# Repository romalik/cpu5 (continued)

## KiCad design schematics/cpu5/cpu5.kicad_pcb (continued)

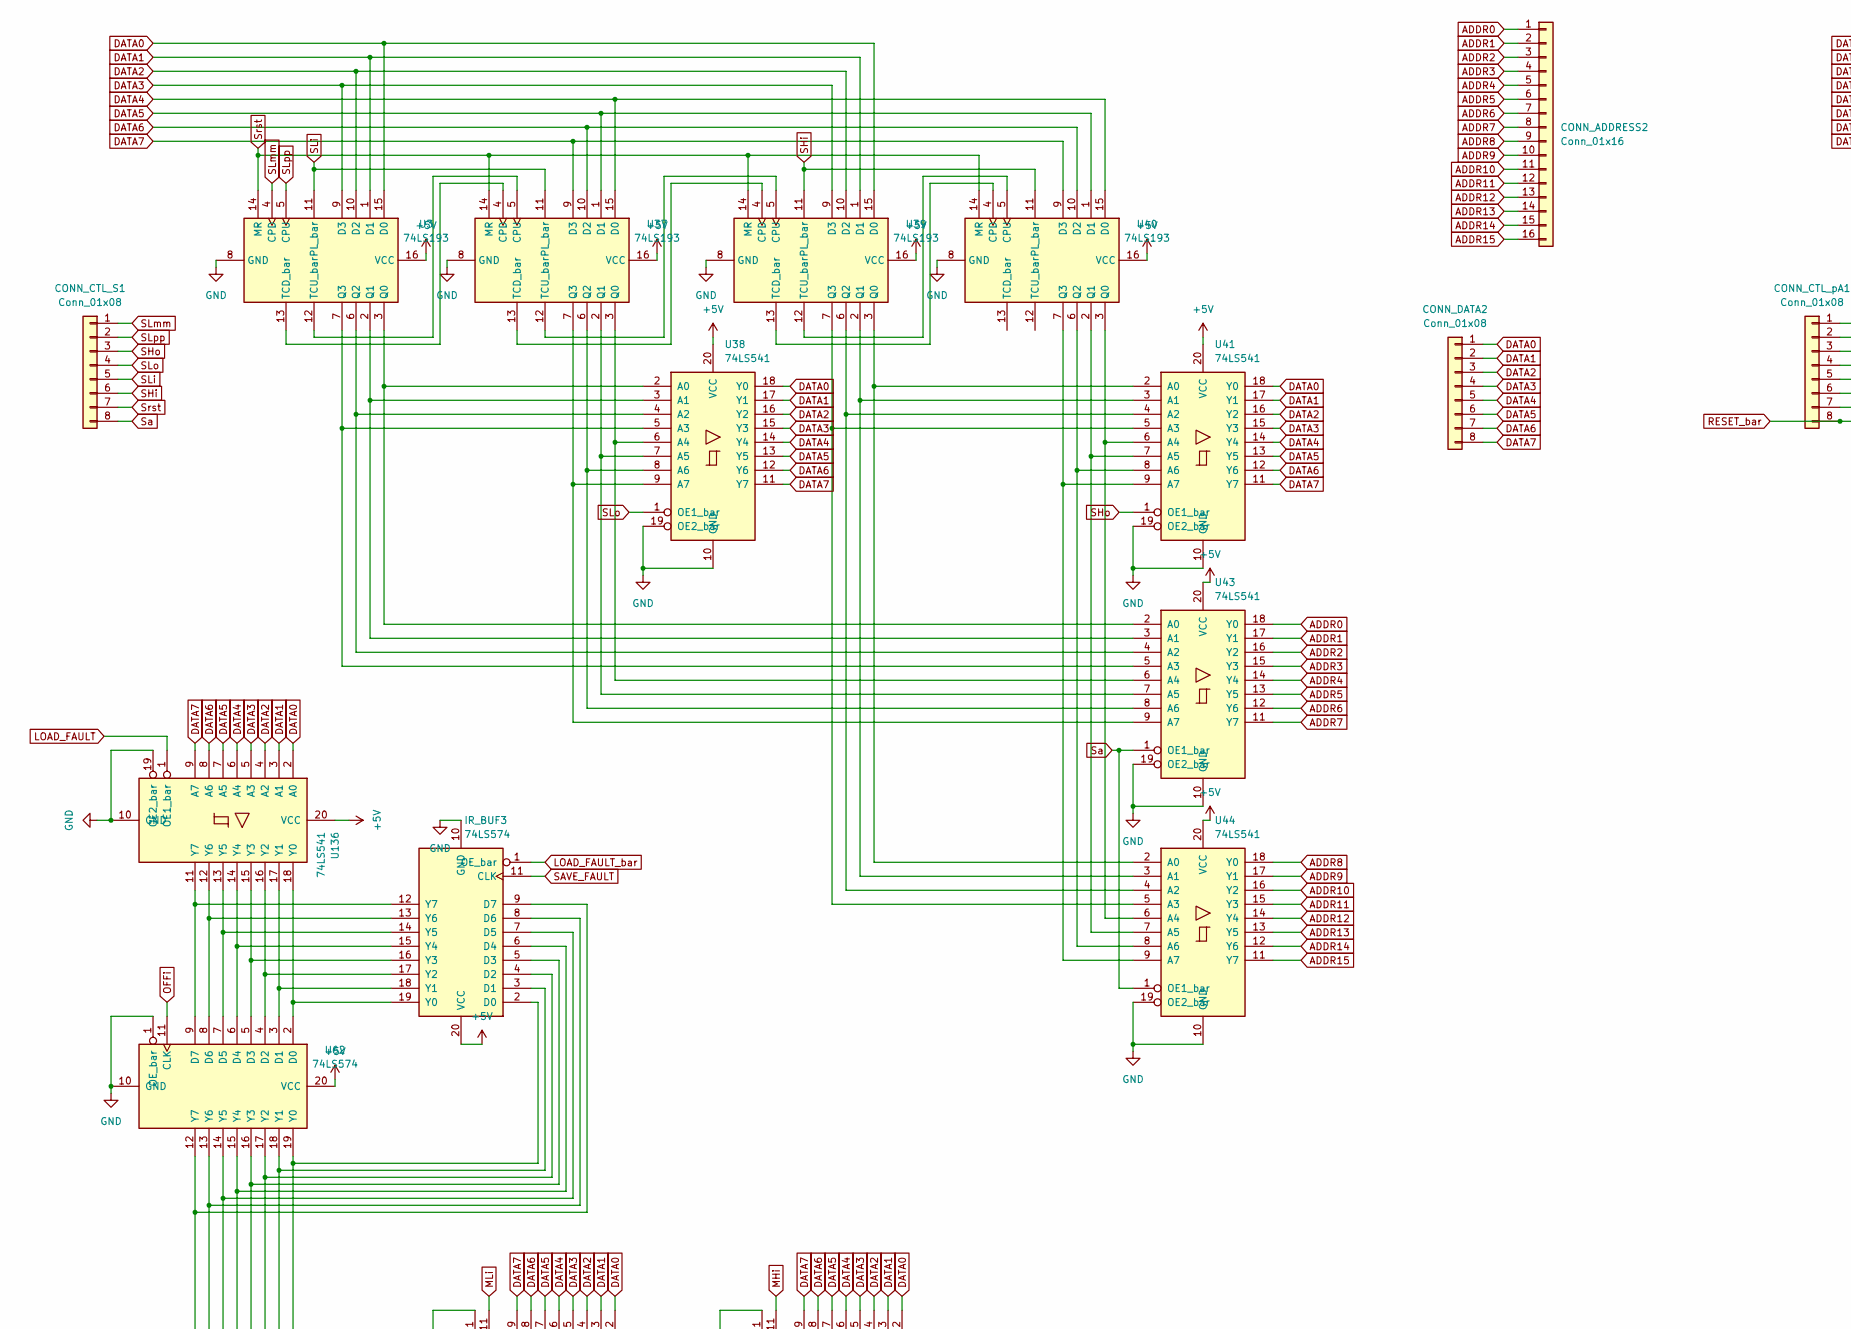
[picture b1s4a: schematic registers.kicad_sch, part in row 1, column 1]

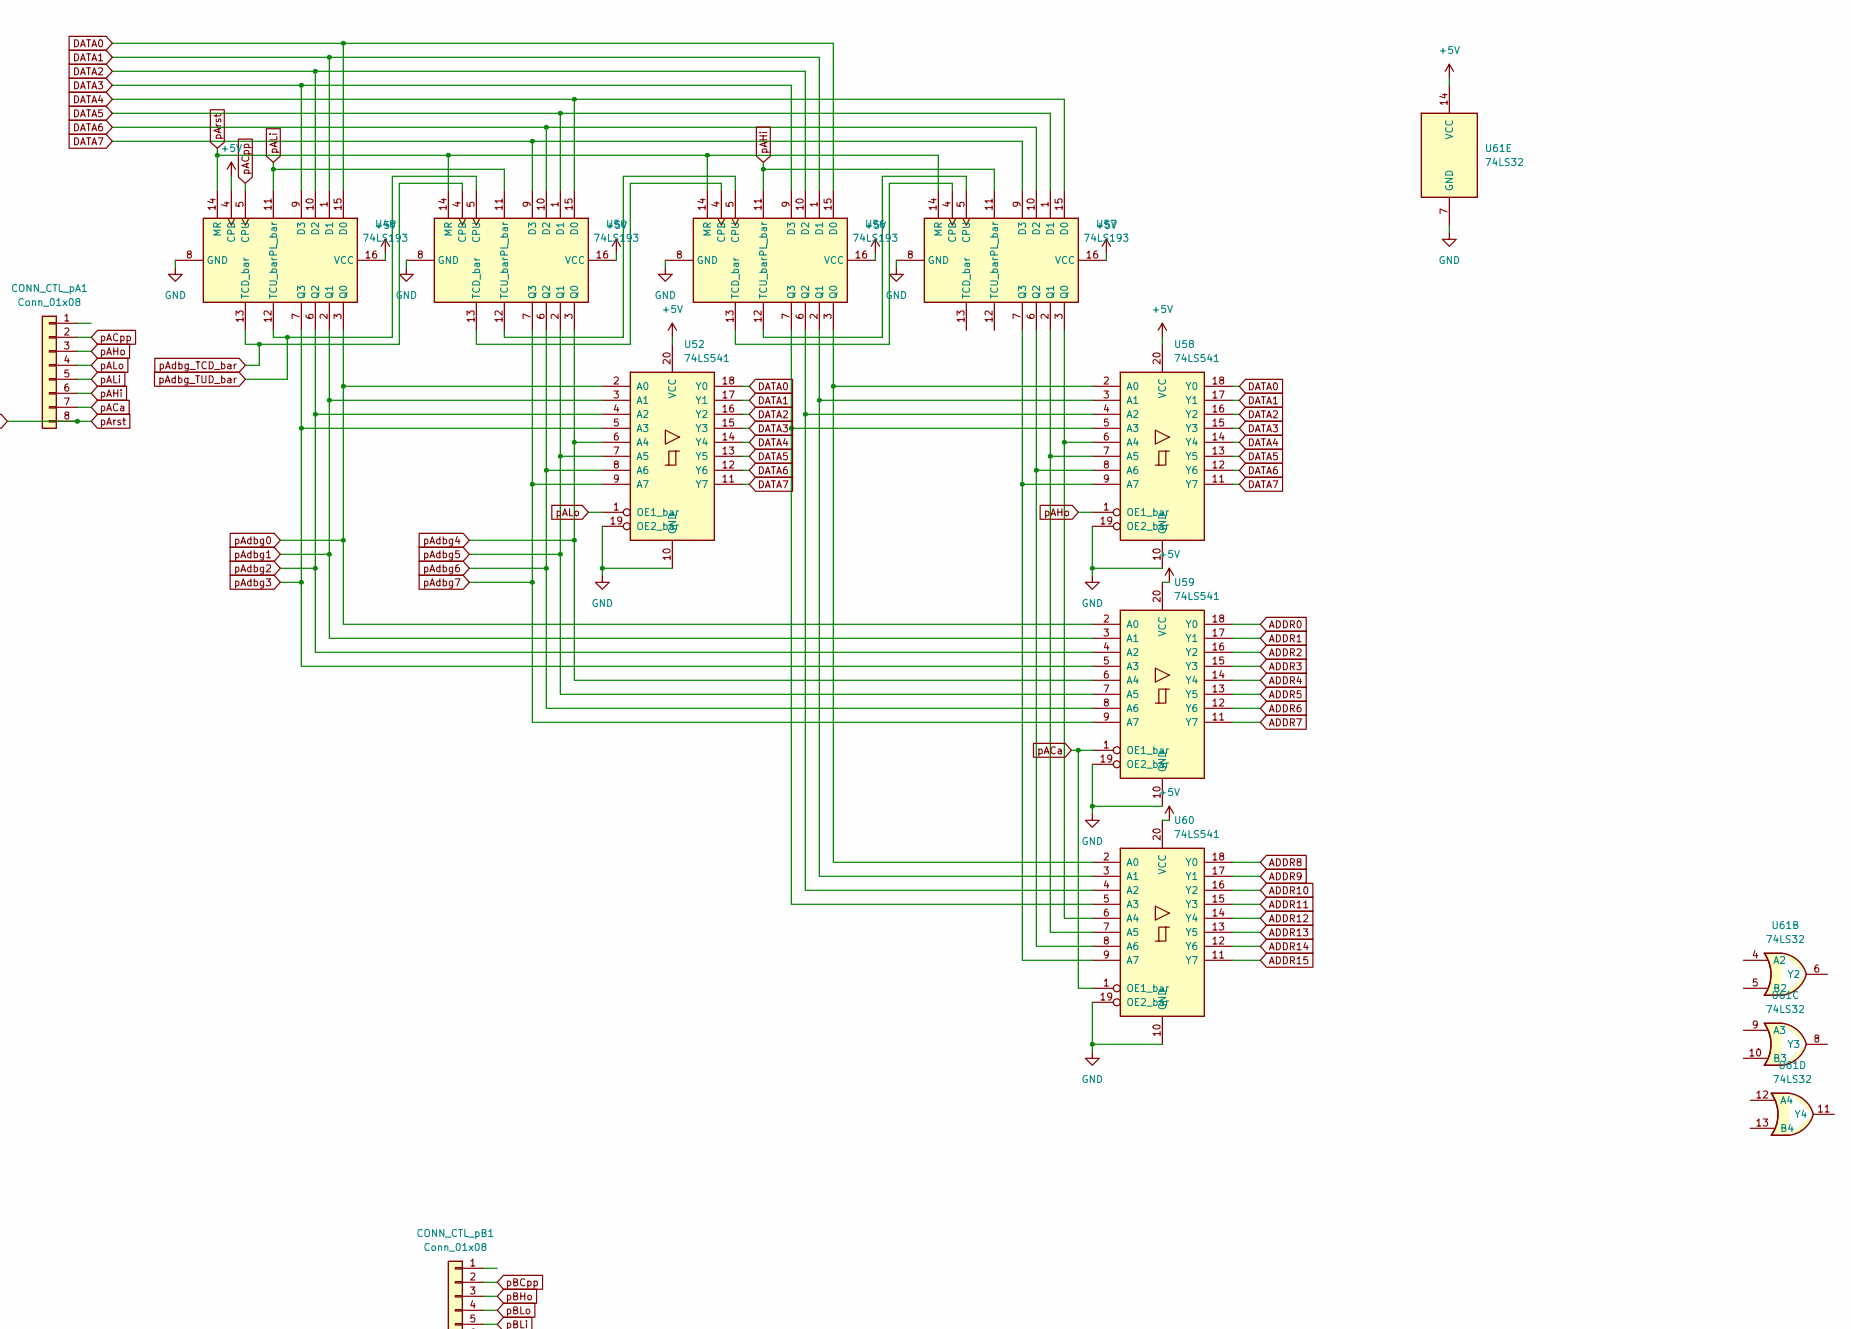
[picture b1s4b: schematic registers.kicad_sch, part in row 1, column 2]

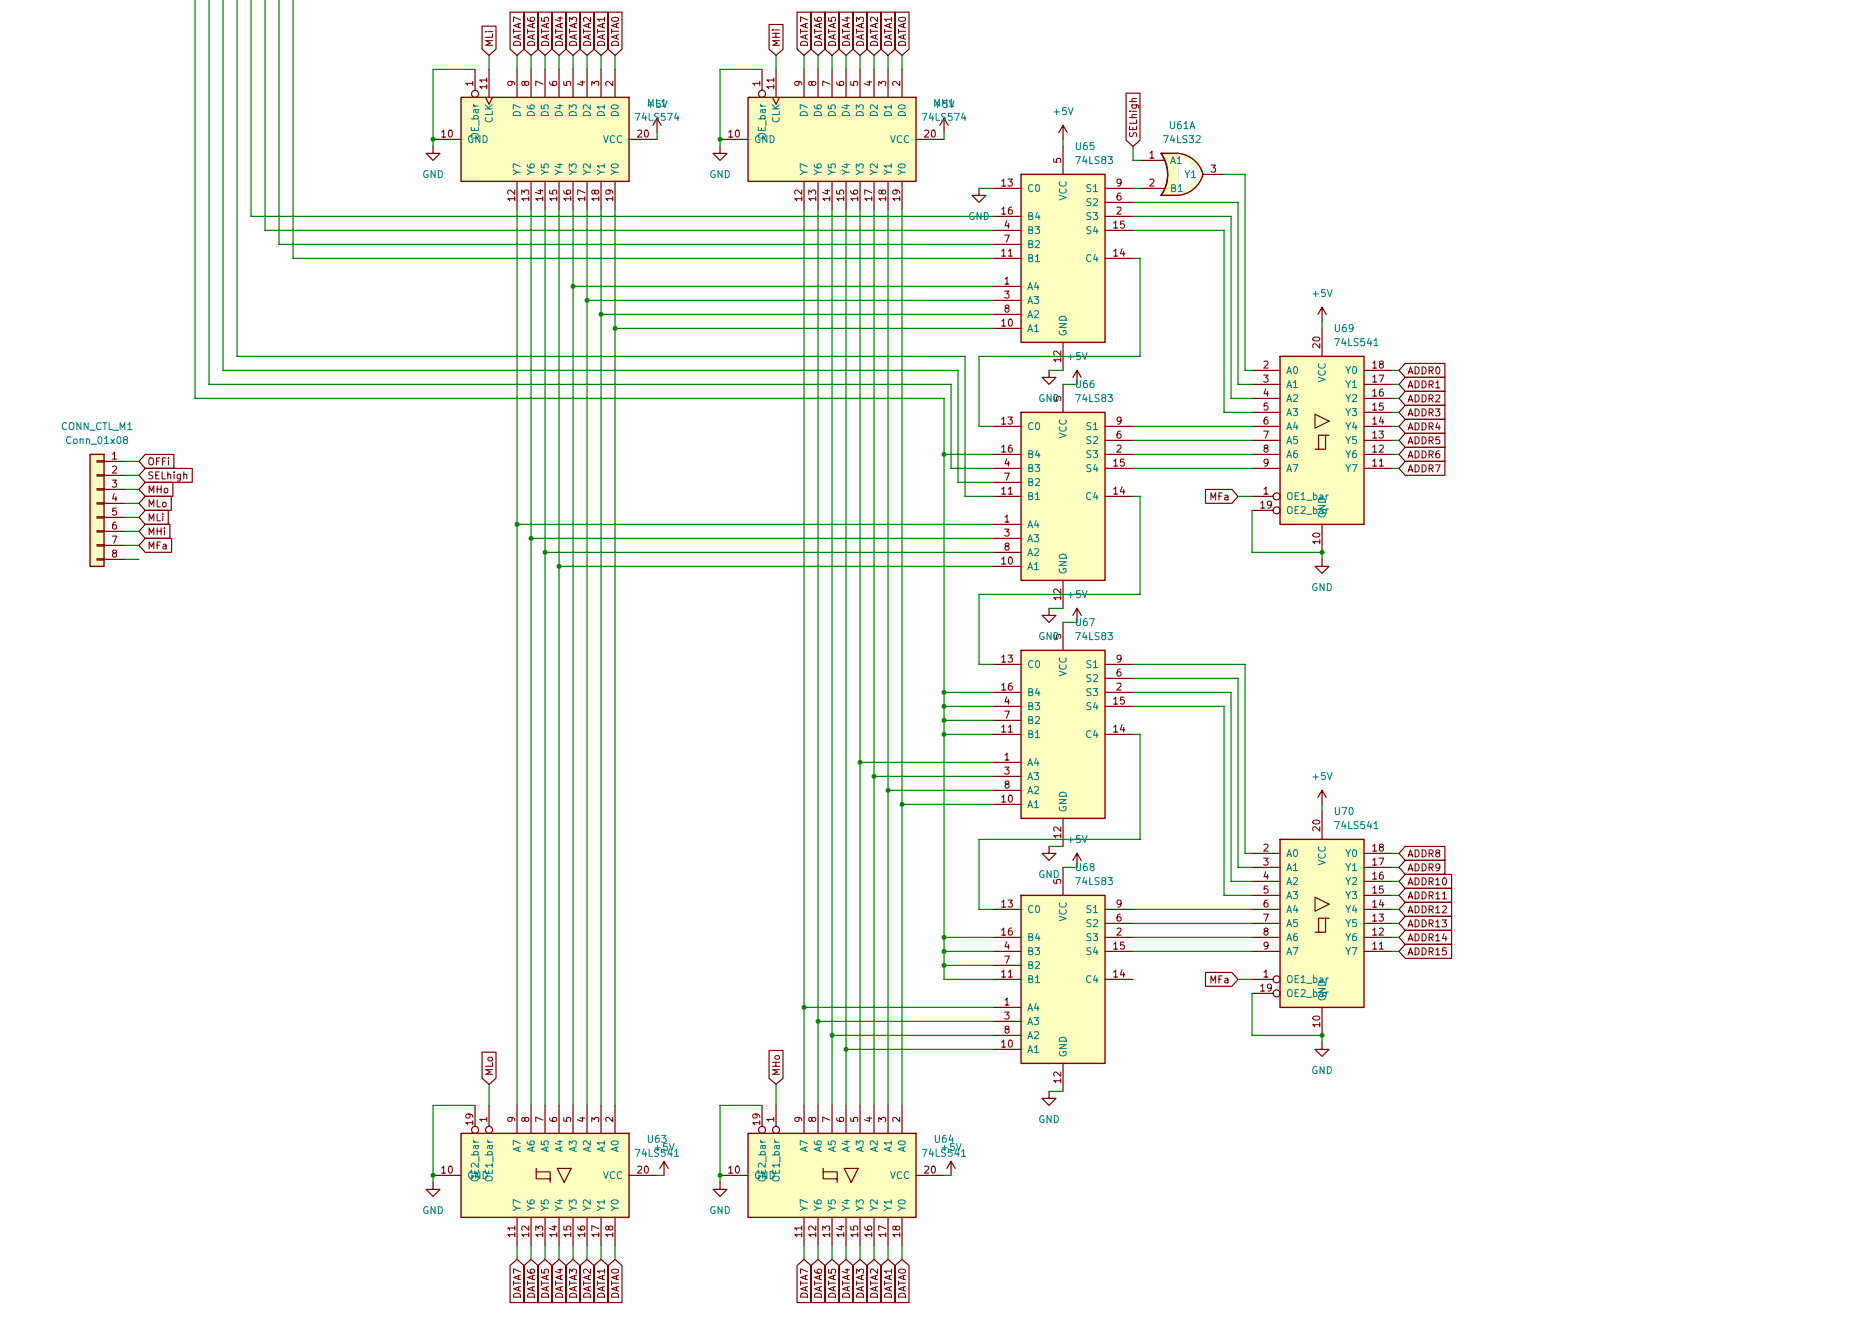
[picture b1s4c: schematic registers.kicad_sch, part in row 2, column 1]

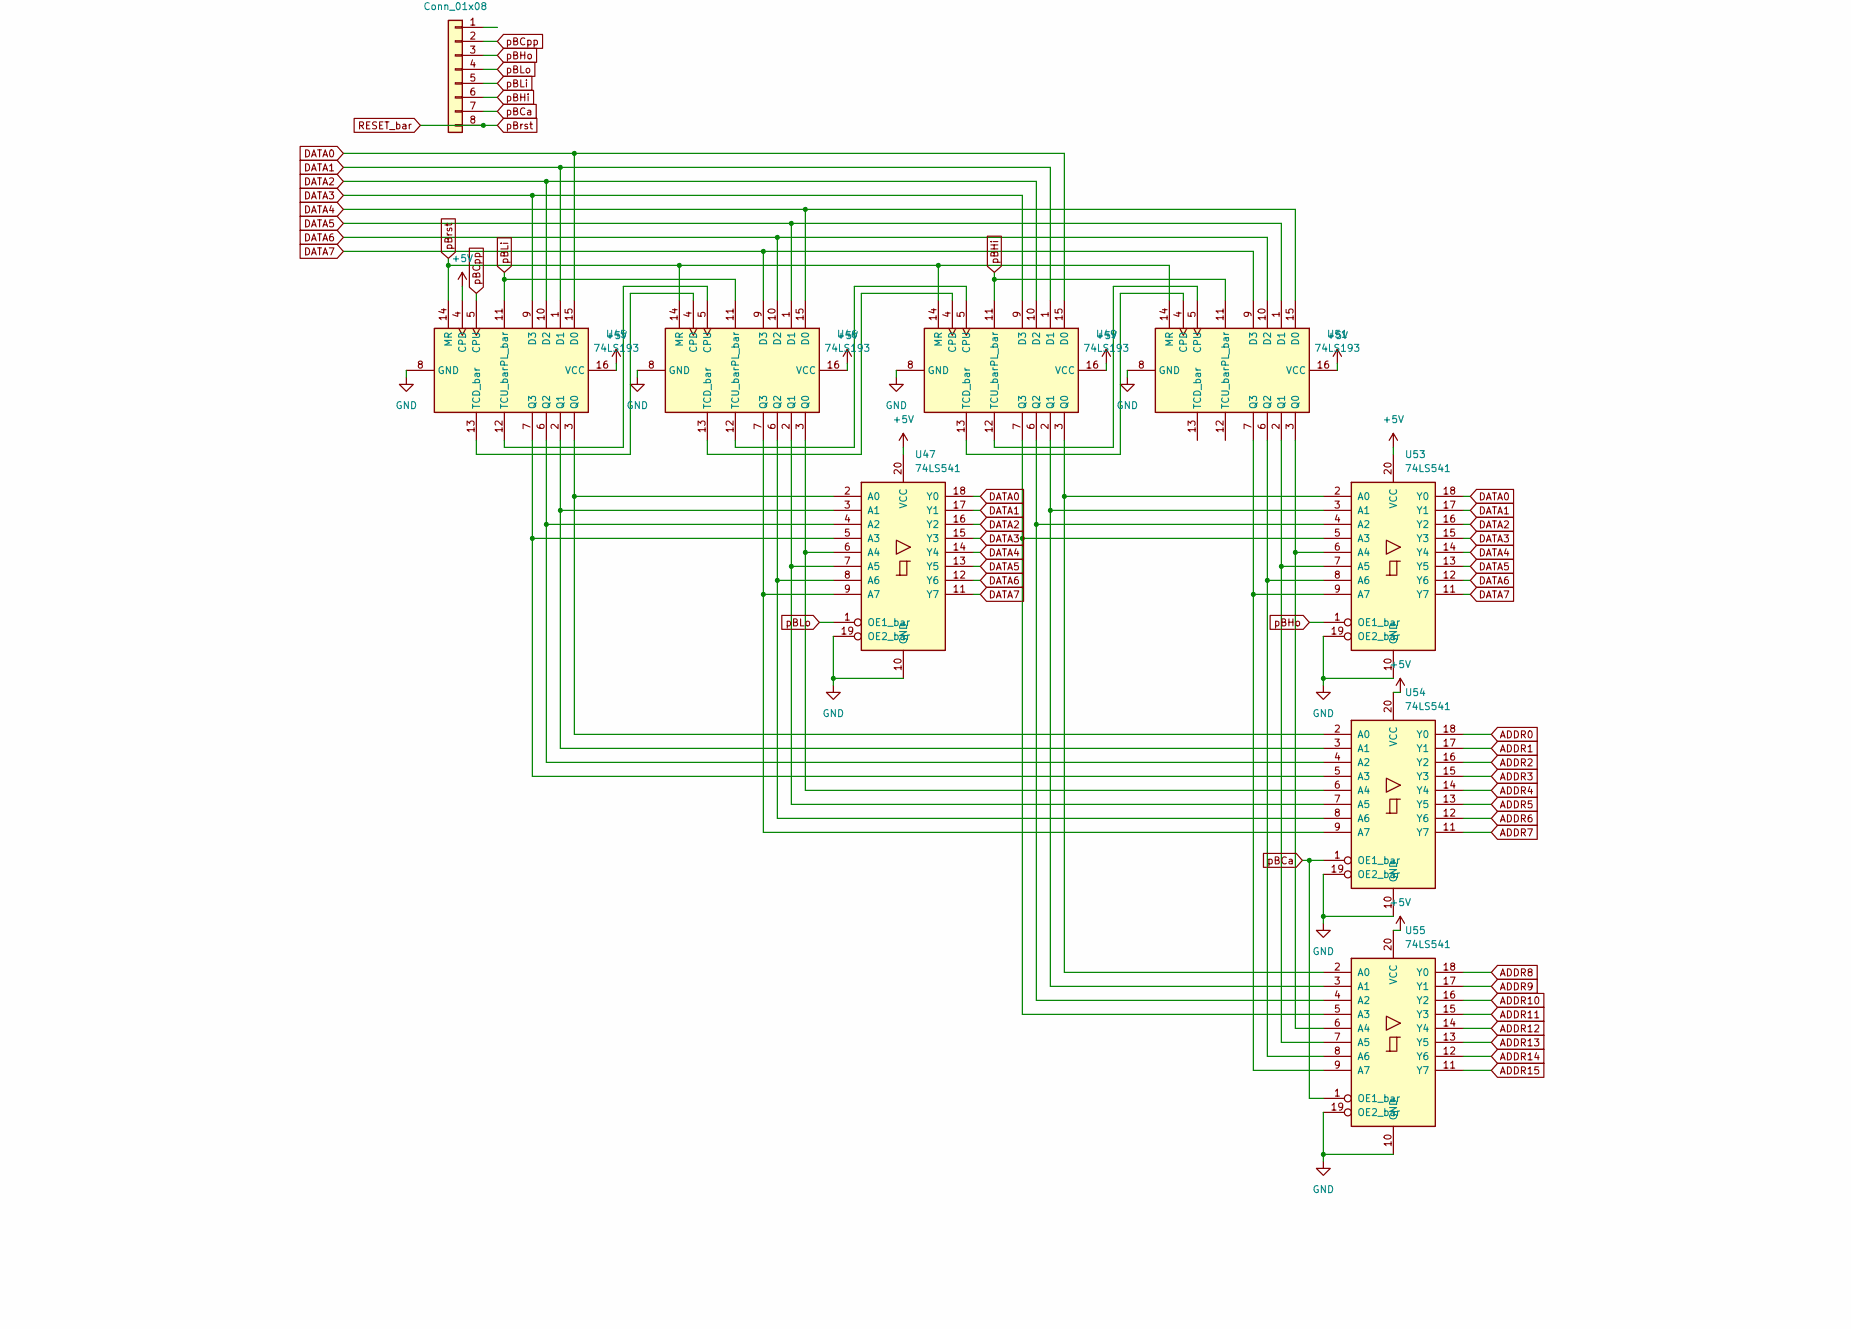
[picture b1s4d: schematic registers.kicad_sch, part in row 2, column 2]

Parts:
CONN_ADDRESS2: Conn_01x16; PinHeader_1x16_P2.54mm_Vertical
CONN_CTL_M1: Conn_01x08; PinHeader_1x08_P2.54mm_Vertical
CONN_CTL_S1: Conn_01x08; PinHeader_1x08_P2.54mm_Vertical
CONN_CTL_pA1: Conn_01x08; PinHeader_1x08_P2.54mm_Vertical
CONN_CTL_pB1: Conn_01x08; PinHeader_1x08_P2.54mm_Vertical
CONN_DATA2: Conn_01x08; PinHeader_1x08_P2.54mm_Vertical
IR_BUF3: 74LS574; DIP-20_W7.62mm
MH1: 74LS574; DIP-20_W7.62mm
ML1: 74LS574; DIP-20_W7.62mm
U3, U37, U39, U40, U45, U46, U48, U49, U50, U51, U56, U57: 74LS193; DIP-16_W7.62mm
U38, U41, U43, U44, U47, U52, U53, U54, U55, U58, U59, U60, U63, U64, U69, U70, U136: 74LS541; DIP-20_W7.62mm
U61: 74LS32; DIP-14_W7.62mm
U62: 74LS574; DIP-20_W7.62mm
U65, U66, U67, U68: 74LS83; DIP-16_W7.62mm

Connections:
+5V: IR_BUF3.20 (VCC), MH1.20 (VCC), ML1.20 (VCC), U3.16 (VCC), U37.16 (VCC), U38.20 (VCC), U39.16 (VCC), U40.16 (VCC), U41.20 (VCC), U43.20 (VCC), U44.20 (VCC), U45.4 (CPD), U45.16 (VCC), U46.16 (VCC), U47.20 (VCC), U48.4 (CPD), U48.16 (VCC), U49.16 (VCC), U50.16 (VCC), U51.16 (VCC), U52.20 (VCC), U53.20 (VCC), U54.20 (VCC), U55.20 (VCC), U56.16 (VCC), U57.16 (VCC), U58.20 (VCC), U59.20 (VCC), U60.20 (VCC), U61.14 (VCC), U62.20 (VCC), U63.20 (VCC), U64.20 (VCC), U65.5 (VCC), U66.5 (VCC), U67.5 (VCC), U68.5 (VCC), U69.20 (VCC), U70.20 (VCC), U136.20 (VCC); also elsewhere on the board
ADDR0: CONN_ADDRESS2.1, U43.18 (Y0), U54.18 (Y0), U59.18 (Y0), U69.18 (Y0); also elsewhere on the board
ADDR1: CONN_ADDRESS2.2, U43.17 (Y1), U54.17 (Y1), U59.17 (Y1), U69.17 (Y1); also elsewhere on the board
ADDR2: CONN_ADDRESS2.3, U43.16 (Y2), U54.16 (Y2), U59.16 (Y2), U69.16 (Y2); also elsewhere on the board
ADDR3: CONN_ADDRESS2.4, U43.15 (Y3), U54.15 (Y3), U59.15 (Y3), U69.15 (Y3); also elsewhere on the board
ADDR4: CONN_ADDRESS2.5, U43.14 (Y4), U54.14 (Y4), U59.14 (Y4), U69.14 (Y4); also elsewhere on the board
ADDR5: CONN_ADDRESS2.6, U43.13 (Y5), U54.13 (Y5), U59.13 (Y5), U69.13 (Y5); also elsewhere on the board
ADDR6: CONN_ADDRESS2.7, U43.12 (Y6), U54.12 (Y6), U59.12 (Y6), U69.12 (Y6); also elsewhere on the board
ADDR7: CONN_ADDRESS2.8, U43.11 (Y7), U54.11 (Y7), U59.11 (Y7), U69.11 (Y7); also elsewhere on the board
ADDR8: CONN_ADDRESS2.9, U44.18 (Y0), U55.18 (Y0), U60.18 (Y0), U70.18 (Y0); also elsewhere on the board
ADDR9: CONN_ADDRESS2.10, U44.17 (Y1), U55.17 (Y1), U60.17 (Y1), U70.17 (Y1); also elsewhere on the board
ADDR10: CONN_ADDRESS2.11, U44.16 (Y2), U55.16 (Y2), U60.16 (Y2), U70.16 (Y2); also elsewhere on the board
ADDR11: CONN_ADDRESS2.12, U44.15 (Y3), U55.15 (Y3), U60.15 (Y3), U70.15 (Y3); also elsewhere on the board
ADDR12: CONN_ADDRESS2.13, U44.14 (Y4), U55.14 (Y4), U60.14 (Y4), U70.14 (Y4); also elsewhere on the board
ADDR13: CONN_ADDRESS2.14, U44.13 (Y5), U55.13 (Y5), U60.13 (Y5), U70.13 (Y5); also elsewhere on the board
ADDR14: CONN_ADDRESS2.15, U44.12 (Y6), U55.12 (Y6), U60.12 (Y6), U70.12 (Y6); also elsewhere on the board
ADDR15: CONN_ADDRESS2.16, U44.11 (Y7), U55.11 (Y7), U60.11 (Y7), U70.11 (Y7); also elsewhere on the board
DATA0: CONN_DATA2.1, MH1.2 (D0), ML1.2 (D0), U3.15 (D0), U38.18 (Y0), U39.15 (D0), U41.18 (Y0), U45.15 (D0), U47.18 (Y0), U48.15 (D0), U49.15 (D0), U52.18 (Y0), U53.18 (Y0), U56.15 (D0), U58.18 (Y0), U63.18 (Y0), U64.18 (Y0), U136.2 (A0); also elsewhere on the board
DATA1: CONN_DATA2.2, MH1.3 (D1), ML1.3 (D1), U3.1 (D1), U38.17 (Y1), U39.1 (D1), U41.17 (Y1), U45.1 (D1), U47.17 (Y1), U48.1 (D1), U49.1 (D1), U52.17 (Y1), U53.17 (Y1), U56.1 (D1), U58.17 (Y1), U63.17 (Y1), U64.17 (Y1), U136.3 (A1); also elsewhere on the board
DATA2: CONN_DATA2.3, MH1.4 (D2), ML1.4 (D2), U3.10 (D2), U38.16 (Y2), U39.10 (D2), U41.16 (Y2), U45.10 (D2), U47.16 (Y2), U48.10 (D2), U49.10 (D2), U52.16 (Y2), U53.16 (Y2), U56.10 (D2), U58.16 (Y2), U63.16 (Y2), U64.16 (Y2), U136.4 (A2); also elsewhere on the board
DATA3: CONN_DATA2.4, MH1.5 (D3), ML1.5 (D3), U3.9 (D3), U38.15 (Y3), U39.9 (D3), U41.15 (Y3), U45.9 (D3), U47.15 (Y3), U48.9 (D3), U49.9 (D3), U52.15 (Y3), U53.15 (Y3), U56.9 (D3), U58.15 (Y3), U63.15 (Y3), U64.15 (Y3), U136.5 (A3); also elsewhere on the board
DATA4: CONN_DATA2.5, MH1.6 (D4), ML1.6 (D4), U37.15 (D0), U38.14 (Y4), U40.15 (D0), U41.14 (Y4), U46.15 (D0), U47.14 (Y4), U50.15 (D0), U51.15 (D0), U52.14 (Y4), U53.14 (Y4), U57.15 (D0), U58.14 (Y4), U63.14 (Y4), U64.14 (Y4), U136.6 (A4); also elsewhere on the board
DATA5: CONN_DATA2.6, MH1.7 (D5), ML1.7 (D5), U37.1 (D1), U38.13 (Y5), U40.1 (D1), U41.13 (Y5), U46.1 (D1), U47.13 (Y5), U50.1 (D1), U51.1 (D1), U52.13 (Y5), U53.13 (Y5), U57.1 (D1), U58.13 (Y5), U63.13 (Y5), U64.13 (Y5), U136.7 (A5); also elsewhere on the board
DATA6: CONN_DATA2.7, MH1.8 (D6), ML1.8 (D6), U37.10 (D2), U38.12 (Y6), U40.10 (D2), U41.12 (Y6), U46.10 (D2), U47.12 (Y6), U50.10 (D2), U51.10 (D2), U52.12 (Y6), U53.12 (Y6), U57.10 (D2), U58.12 (Y6), U63.12 (Y6), U64.12 (Y6), U136.8 (A6); also elsewhere on the board
DATA7: CONN_DATA2.8, MH1.9 (D7), ML1.9 (D7), U37.9 (D3), U38.11 (Y7), U40.9 (D3), U41.11 (Y7), U46.9 (D3), U47.11 (Y7), U50.9 (D3), U51.9 (D3), U52.11 (Y7), U53.11 (Y7), U57.9 (D3), U58.11 (Y7), U63.11 (Y7), U64.11 (Y7), U136.9 (A7); also elsewhere on the board
GND: IR_BUF3.10 (GND), MH1.1 (OE_bar), MH1.10 (GND), ML1.1 (OE_bar), ML1.10 (GND), U3.8 (GND), U37.8 (GND), U38.10 (GND), U38.19 (OE2_bar), U39.8 (GND), U40.8 (GND), U41.10 (GND), U41.19 (OE2_bar), U43.10 (GND), U43.19 (OE2_bar), U44.10 (GND), U44.19 (OE2_bar), U45.8 (GND), U46.8 (GND), U47.10 (GND), U47.19 (OE2_bar), U48.8 (GND), U49.8 (GND), U50.8 (GND), U51.8 (GND), U52.10 (GND), U52.19 (OE2_bar), U53.10 (GND), U53.19 (OE2_bar), U54.10 (GND), U54.19 (OE2_bar), U55.10 (GND), U55.19 (OE2_bar), U56.8 (GND), U57.8 (GND), U58.10 (GND), U58.19 (OE2_bar), U59.10 (GND), U59.19 (OE2_bar), U60.10 (GND), U60.19 (OE2_bar), U61.7 (GND), U62.1 (OE_bar), U62.10 (GND), U63.10 (GND), U63.19 (OE2_bar), U64.10 (GND), U64.19 (OE2_bar), U65.12 (GND), U65.13 (C0), U66.12 (GND), U67.12 (GND), U68.12 (GND), U69.10 (GND), U69.19 (OE2_bar), U70.10 (GND), U70.19 (OE2_bar), U136.10 (GND), U136.19 (OE2_bar); also elsewhere on the board
LOAD_FAULT: U136.1 (OE1_bar); also elsewhere on the board
LOAD_FAULT_bar: IR_BUF3.1 (OE_bar); also elsewhere on the board
MFa: CONN_CTL_M1.7, U69.1 (OE1_bar), U70.1 (OE1_bar); also elsewhere on the board
MHi: CONN_CTL_M1.6, MH1.11 (CLK); also elsewhere on the board
MHo: CONN_CTL_M1.3, U64.1 (OE1_bar); also elsewhere on the board
MLi: CONN_CTL_M1.5, ML1.11 (CLK); also elsewhere on the board
MLo: CONN_CTL_M1.4, U63.1 (OE1_bar); also elsewhere on the board
unnamed: IR_BUF3.2 (D0), U62.19 (Y0), U65.11 (B1)
unnamed: IR_BUF3.3 (D1), U62.18 (Y1), U65.7 (B2)
unnamed: IR_BUF3.4 (D2), U62.17 (Y2), U65.4 (B3)
unnamed: IR_BUF3.5 (D3), U62.16 (Y3), U65.16 (B4)
unnamed: IR_BUF3.6 (D4), U62.15 (Y4), U66.11 (B1)
unnamed: IR_BUF3.7 (D5), U62.14 (Y5), U66.7 (B2)
unnamed: IR_BUF3.8 (D6), U62.13 (Y6), U66.4 (B3)
unnamed: IR_BUF3.9 (D7), U62.12 (Y7), U66.16 (B4), U67.4 (B3), U67.7 (B2), U67.11 (B1), U67.16 (B4), U68.4 (B3), U68.7 (B2), U68.11 (B1), U68.16 (B4)
unnamed: IR_BUF3.12 (Y7), U62.9 (D7), U136.11 (Y7)
unnamed: IR_BUF3.13 (Y6), U62.8 (D6), U136.12 (Y6)
unnamed: IR_BUF3.14 (Y5), U62.7 (D5), U136.13 (Y5)
unnamed: IR_BUF3.15 (Y4), U62.6 (D4), U136.14 (Y4)
unnamed: IR_BUF3.16 (Y3), U62.5 (D3), U136.15 (Y3)
unnamed: IR_BUF3.17 (Y2), U62.4 (D2), U136.16 (Y2)
unnamed: IR_BUF3.18 (Y1), U62.3 (D1), U136.17 (Y1)
unnamed: IR_BUF3.19 (Y0), U62.2 (D0), U136.18 (Y0)
unnamed: MH1.12 (Y7), U64.9 (A7), U68.1 (A4)
unnamed: MH1.13 (Y6), U64.8 (A6), U68.3 (A3)
unnamed: MH1.14 (Y5), U64.7 (A5), U68.8 (A2)
unnamed: MH1.15 (Y4), U64.6 (A4), U68.10 (A1)
unnamed: MH1.16 (Y3), U64.5 (A3), U67.1 (A4)
unnamed: MH1.17 (Y2), U64.4 (A2), U67.3 (A3)
unnamed: MH1.18 (Y1), U64.3 (A1), U67.8 (A2)
unnamed: MH1.19 (Y0), U64.2 (A0), U67.10 (A1)
unnamed: ML1.12 (Y7), U63.9 (A7), U66.1 (A4)
unnamed: ML1.13 (Y6), U63.8 (A6), U66.3 (A3)
unnamed: ML1.14 (Y5), U63.7 (A5), U66.8 (A2)
unnamed: ML1.15 (Y4), U63.6 (A4), U66.10 (A1)
unnamed: ML1.16 (Y3), U63.5 (A3), U65.1 (A4)
unnamed: ML1.17 (Y2), U63.4 (A2), U65.3 (A3)
unnamed: ML1.18 (Y1), U63.3 (A1), U65.8 (A2)
unnamed: ML1.19 (Y0), U63.2 (A0), U65.10 (A1)
unnamed: U3.2 (Q1), U38.3 (A1), U43.3 (A1)
unnamed: U3.3 (Q0), U38.2 (A0), U43.2 (A0)
unnamed: U3.6 (Q2), U38.4 (A2), U43.4 (A2)
unnamed: U3.7 (Q3), U38.5 (A3), U43.5 (A3)
unnamed: U3.12 (TCU_bar), U37.5 (CPU)
unnamed: U3.13 (TCD_bar), U37.4 (CPD)
unnamed: U37.2 (Q1), U38.7 (A5), U43.7 (A5)
unnamed: U37.3 (Q0), U38.6 (A4), U43.6 (A4)
unnamed: U37.6 (Q2), U38.8 (A6), U43.8 (A6)
unnamed: U37.7 (Q3), U38.9 (A7), U43.9 (A7)
unnamed: U37.12 (TCU_bar), U39.5 (CPU)
unnamed: U37.13 (TCD_bar), U39.4 (CPD)
unnamed: U39.2 (Q1), U41.3 (A1), U44.3 (A1)
unnamed: U39.3 (Q0), U41.2 (A0), U44.2 (A0)
unnamed: U39.6 (Q2), U41.4 (A2), U44.4 (A2)
unnamed: U39.7 (Q3), U41.5 (A3), U44.5 (A3)
unnamed: U39.12 (TCU_bar), U40.5 (CPU)
unnamed: U39.13 (TCD_bar), U40.4 (CPD)
unnamed: U40.2 (Q1), U41.7 (A5), U44.7 (A5)
unnamed: U40.3 (Q0), U41.6 (A4), U44.6 (A4)
unnamed: U40.6 (Q2), U41.8 (A6), U44.8 (A6)
unnamed: U40.7 (Q3), U41.9 (A7), U44.9 (A7)
unnamed: U45.2 (Q1), U47.3 (A1), U54.3 (A1)
unnamed: U45.3 (Q0), U47.2 (A0), U54.2 (A0)
unnamed: U45.6 (Q2), U47.4 (A2), U54.4 (A2)
unnamed: U45.7 (Q3), U47.5 (A3), U54.5 (A3)
unnamed: U45.12 (TCU_bar), U46.5 (CPU)
unnamed: U45.13 (TCD_bar), U46.4 (CPD)
unnamed: U46.2 (Q1), U47.7 (A5), U54.7 (A5)
unnamed: U46.3 (Q0), U47.6 (A4), U54.6 (A4)
unnamed: U46.6 (Q2), U47.8 (A6), U54.8 (A6)
unnamed: U46.7 (Q3), U47.9 (A7), U54.9 (A7)
unnamed: U46.12 (TCU_bar), U49.5 (CPU)
unnamed: U46.13 (TCD_bar), U49.4 (CPD)
unnamed: U49.2 (Q1), U53.3 (A1), U55.3 (A1)
unnamed: U49.3 (Q0), U53.2 (A0), U55.2 (A0)
unnamed: U49.6 (Q2), U53.4 (A2), U55.4 (A2)
unnamed: U49.7 (Q3), U53.5 (A3), U55.5 (A3)
unnamed: U49.12 (TCU_bar), U51.5 (CPU)
unnamed: U49.13 (TCD_bar), U51.4 (CPD)
unnamed: U50.12 (TCU_bar), U56.5 (CPU)
unnamed: U50.13 (TCD_bar), U56.4 (CPD)
unnamed: U51.2 (Q1), U53.7 (A5), U55.7 (A5)
unnamed: U51.3 (Q0), U53.6 (A4), U55.6 (A4)
unnamed: U51.6 (Q2), U53.8 (A6), U55.8 (A6)
unnamed: U51.7 (Q3), U53.9 (A7), U55.9 (A7)
unnamed: U56.2 (Q1), U58.3 (A1), U60.3 (A1)
unnamed: U56.3 (Q0), U58.2 (A0), U60.2 (A0)
unnamed: U56.6 (Q2), U58.4 (A2), U60.4 (A2)
unnamed: U56.7 (Q3), U58.5 (A3), U60.5 (A3)
unnamed: U56.12 (TCU_bar), U57.5 (CPU)
unnamed: U56.13 (TCD_bar), U57.4 (CPD)
unnamed: U57.2 (Q1), U58.7 (A5), U60.7 (A5)
unnamed: U57.3 (Q0), U58.6 (A4), U60.6 (A4)
unnamed: U57.6 (Q2), U58.8 (A6), U60.8 (A6)
unnamed: U57.7 (Q3), U58.9 (A7), U60.9 (A7)
unnamed: U61.2 (B1), U65.9 (S1)
unnamed: U61.3 (Y1), U69.2 (A0)
unnamed: U65.2 (S3), U69.4 (A2)
unnamed: U65.6 (S2), U69.3 (A1)
unnamed: U65.14 (C4), U66.13 (C0)
unnamed: U65.15 (S4), U69.5 (A3)
unnamed: U66.2 (S3), U69.8 (A6)
unnamed: U66.6 (S2), U69.7 (A5)
unnamed: U66.9 (S1), U69.6 (A4)
unnamed: U66.14 (C4), U67.13 (C0)
unnamed: U66.15 (S4), U69.9 (A7)
unnamed: U67.2 (S3), U70.4 (A2)
unnamed: U67.6 (S2), U70.3 (A1)
unnamed: U67.9 (S1), U70.2 (A0)
unnamed: U67.14 (C4), U68.13 (C0)
unnamed: U67.15 (S4), U70.5 (A3)
unnamed: U68.2 (S3), U70.8 (A6)
unnamed: U68.6 (S2), U70.7 (A5)
unnamed: U68.9 (S1), U70.6 (A4)
unnamed: U68.15 (S4), U70.9 (A7)
OFFi: CONN_CTL_M1.1, U62.11 (CLK); also elsewhere on the board
RESET_bar: CONN_CTL_pA1.8, CONN_CTL_pB1.8, U45.14 (MR), U46.14 (MR), U48.14 (MR), U49.14 (MR), U50.14 (MR), U51.14 (MR), U56.14 (MR), U57.14 (MR); also elsewhere on the board
SAVE_FAULT: IR_BUF3.11 (CLK); also elsewhere on the board
SELhigh: CONN_CTL_M1.2, U61.1 (A1); also elsewhere on the board
SHi: CONN_CTL_S1.6, U39.11 (PL_bar), U40.11 (PL_bar); also elsewhere on the board
SHo: CONN_CTL_S1.3, U41.1 (OE1_bar); also elsewhere on the board
SLi: CONN_CTL_S1.5, U3.11 (PL_bar), U37.11 (PL_bar); also elsewhere on the board
SLmm: CONN_CTL_S1.1, U3.4 (CPD); also elsewhere on the board
SLo: CONN_CTL_S1.4, U38.1 (OE1_bar); also elsewhere on the board
SLpp: CONN_CTL_S1.2, U3.5 (CPU); also elsewhere on the board
Sa: CONN_CTL_S1.8, U43.1 (OE1_bar), U44.1 (OE1_bar); also elsewhere on the board
Srst: CONN_CTL_S1.7, U3.14 (MR), U37.14 (MR), U39.14 (MR), U40.14 (MR); also elsewhere on the board
pACa: CONN_CTL_pA1.7, U59.1 (OE1_bar), U60.1 (OE1_bar); also elsewhere on the board
pACpp: CONN_CTL_pA1.2, U48.5 (CPU); also elsewhere on the board
pAHi: CONN_CTL_pA1.6, U56.11 (PL_bar), U57.11 (PL_bar); also elsewhere on the board
pAHo: CONN_CTL_pA1.3, U58.1 (OE1_bar); also elsewhere on the board
pALi: CONN_CTL_pA1.5, U48.11 (PL_bar), U50.11 (PL_bar); also elsewhere on the board
pALo: CONN_CTL_pA1.4, U52.1 (OE1_bar); also elsewhere on the board
pAdbg0: U48.3 (Q0), U52.2 (A0), U59.2 (A0)
pAdbg1: U48.2 (Q1), U52.3 (A1), U59.3 (A1)
pAdbg2: U48.6 (Q2), U52.4 (A2), U59.4 (A2)
pAdbg3: U48.7 (Q3), U52.5 (A3), U59.5 (A3)
pAdbg4: U50.3 (Q0), U52.6 (A4), U59.6 (A4)
pAdbg5: U50.2 (Q1), U52.7 (A5), U59.7 (A5)
pAdbg6: U50.6 (Q2), U52.8 (A6), U59.8 (A6)
pAdbg7: U50.7 (Q3), U52.9 (A7), U59.9 (A7)
pAdbg_TCD_bar: U48.13 (TCD_bar), U50.4 (CPD)
pAdbg_TUD_bar: U48.12 (TCU_bar), U50.5 (CPU)
pBCa: CONN_CTL_pB1.7, U54.1 (OE1_bar), U55.1 (OE1_bar); also elsewhere on the board
pBCpp: CONN_CTL_pB1.2, U45.5 (CPU); also elsewhere on the board
pBHi: CONN_CTL_pB1.6, U49.11 (PL_bar), U51.11 (PL_bar); also elsewhere on the board
pBHo: CONN_CTL_pB1.3, U53.1 (OE1_bar); also elsewhere on the board
pBLi: CONN_CTL_pB1.5, U45.11 (PL_bar), U46.11 (PL_bar); also elsewhere on the board
pBLo: CONN_CTL_pB1.4, U47.1 (OE1_bar); also elsewhere on the board
